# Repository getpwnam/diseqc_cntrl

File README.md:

# diseqc_cntrl

Ethernet-connected DiSEqC motor control interface for satellite LNB systems, built around an STM32F407 microcontroller.

## Disclaimer

This project is in active development and use is at your own risk. Core firmware,
managed deployment, X.509 provisioning, TLS 1.3, and read-only REST API flows
have been exercised on Cubley v0.5 hardware; this is not a production safety
certification.

## Quick Start

For the tested firmware-to-HTTPS path:

1. Build and flash the firmware.
2. Build and deploy `CubleyControl` over the nanoFramework wire protocol.
3. Provision a unique X.509 device credential.
4. Trust the public certificate and verify `/api/v2/health`.
5. Optionally configure an API token over the USB CDC console.

Follow [HTTPS Transport](docs/software/HTTPS_TRANSPORT.md) for the complete
copy-and-paste sequence. The API client is [tools/cubleyctl.py](tools/cubleyctl.py);
the API guide is
[DEVICE_API_V2_DEVELOPER_GUIDE.md](docs/software/DEVICE_API_V2_DEVELOPER_GUIDE.md).

## Introduction

Enables remote control of LNB power supply voltage (13 V / 18 V polarization selection), DiSEqC 1.x command generation, and IF signal routing — all manageable over a 10/100 Mbps Ethernet link or USB.

## Repository Structure

The project is intentionally split into separate domains:

1. `hardware/`  
	KiCad schematics, PCB layout, fabrication outputs, and hardware-specific assets.
2. `software/nanoFramework/`  
	Managed application + native integration layer used by this project.
3. `nf-interpreter` (external dependency at build time)  
	The nanoFramework/ChibiOS firmware base is cloned during build and patched with this repository's target files.

See:
- `hardware/README.md`
- `software/README.md`
- `software/nanoFramework/README.md`

## PCB

4-layer board (F.Cu / In1.Cu / In2.Cu / B.Cu) with split ground planes — digital GND, analog GNDA, and power PGND domains are connected via net ties at controlled star-ground points to minimise noise coupling into the LNB signal path.

## Hardware Overview

### Microcontroller

- **STM32F407VGT6** (ARM Cortex-M4, 168 MHz, 1 MB Flash, 192 KB RAM, LQFP-100)
- 8 MHz HSE crystal (ABLS-8.000MHZ-20-B-3-H-T) on PH0/PH1 with C15/C18 load capacitors
- Separate filtered +3V3_ANA rail for the on-chip ADC reference
- Status LED (green, 0603)

### Key peripherals used

| Peripheral | Function |
| --- | --- |
| I2C1 | LNBH26PQR LNB supply controller |
| I2C3 | FM24CL16B 16 Kb F-RAM and expansion header |
| Ethernet MAC (RMII) | LAN8742A 10/100 Ethernet PHY |
| TIM4 CH1 | DiSEqC 22 kHz tone generation |
| USART3 | Serial debug / expansion (pin header J2) |
| USB OTG FS | USB 2.0 device (USB-C) |
| SWD | Debug port (2×5 pin header J5) |

### Power Supply

**Input:** Barrel jack (RASM742TRX, 2.1 mm centre-positive)

Protection chain (in order):

1. **F1** — PTC resettable fuse (1812L075/33DR, 0.75 A hold / 33 V)
2. **D2** — SMBJ24D bidirectional TVS (24 V clamp)
3. **D1** — SS14F-HF Schottky diode (reverse polarity protection)

Regulation:

| Stage | Device | Topology | Output |
| --- | --- | --- | --- |
| 1 | PS1 (TPS560430XDBVR) | Synchronous buck (4.3–36 V in) | +12 V (feeds LNBH26PQR) |
| 2 | TPS560200DBVR | Buck (4.5–17 V in) | +3.3 V (digital logic) |

A filtered +3V3_ANA rail is derived from +3.3 V via a ferrite bead for the MCU analog supply.

### LNB Control — LNBH26PQR

- Dual LNB supply regulator with integrated step-up converter (ST LNBH26PQR, QFN-24)
- Powered from the +12 V rail
- Generates switchable 13 V / 18 V output for LNB polarization selection
- Built-in DiSEqC 1.x/2.x 22 kHz tone modulation, driven from TIM4 CH1
- Fault output routed to MCU GPIO
- External boost components: STPS130A Schottky, US1A rectifier, 33 µH inductor, 100 µF bulk caps
- DiSEqC envelope detection via BAT43XV2 small-signal Schottky
- ESD protection on coaxial outputs (RCLAMP0502BATCT)

### Ethernet

- STM32F407 integrated 10/100 Ethernet MAC connected over RMII
- **LAN8742A-CZ-TR** 10/100 Ethernet PHY (Microchip, SQFN-24)
- 25 MHz PHY crystal (ABLS-25.000MHZ-D-FT)
- **J0011D21BNL** RJ45 connector with integrated magnetics and link/activity LEDs

### USB

- **USB4110-GF-A** USB Type-C receptacle (USB 2.0)
- **USBLC6-2P6** ESD protection on D+/D−
- Connected to STM32 USB OTG FS peripheral

### Non-Volatile Storage

- **FM24CL16B-GTR** 16 Kb F-RAM (Infineon, I2C, SOIC-8)
- Unlimited write endurance — stores network configuration, LNB settings, and DiSEqC sequence parameters

### Connectors

| Ref | Type | Purpose |
| --- | --- | --- |
| J1 | Barrel jack (RASM742TRX) | DC power input |
| J2 | 1×4 pin header (2.00 mm) | USART3 serial header (+3V3, TX, RX, GND) |
| J3 | 1×4 pin header (2.00 mm) | I2C3 expansion header (+3V3, SCL, SDA, GND) |
| J4 | USB-C (USB4110-GF-A) | USB 2.0 device |
| J5 | 2×5 pin header (2.54 mm) | SWD debug |
| J6 | SMA edge-mount | IF input from LNB |
| J7 | SMA edge-mount | LNB output (power + DiSEqC + IF) |
| J9 | RJ45 (J0011D21BNL) | 10/100 Ethernet with integrated magnetics and LEDs |
| S1 | SPDT slide switch (PCM12SMTBR) | Mode / power select |

### Test Points

| Ref | Net | Purpose |
| --- | --- | --- |
| TP1 | VIN_FUSED | Input rail after PTC fuse |
| TP2 | +12V | Main regulated 12 V rail |
| TP3 | +3V3 | Main digital logic rail |
| TP4 | VIN_RAW | Input rail before fuse/protection chain |
| TP5 | VIN_PROTECTED | Input rail after TVS and reverse-polarity diode |
| TP6 | +3V3_ANA | Filtered analog 3.3 V rail |
| TP7 | VSSA | Analog ground reference |
| TP8 | /MCU/BOOT0 | MCU BOOT0 strap node |
| TP9 | VBUS | USB VBUS (5 V) |
| TP10 | /MCU/CC1 | USB-C CC1 configuration channel |
| TP11 | /MCU/CC2 | USB-C CC2 configuration channel |
| TP12 | IF_OUT | IF signal path node |
| TP13 | LNB_OUT | LNB output node |
| TP14 | /MCU/LNBH26PQR/LNB_FLT | LNB controller fault signal |

### Protection

| Component | Type | Location |
| --- | --- | --- |
| F1 (1812L075/33DR) | PTC fuse, 0.75 A / 33 V | Power input |
| D2 (SMBJ24D) | 24 V bidirectional TVS | After fuse |
| D1 (SS14F-HF) | Schottky reverse polarity | After TVS |
| IC3 (USBLC6-2P6) | USB ESD clamp | USB D+/D− |
| D7 (RCLAMP0502BATCT) | ESD / CDE clamp | LNB coaxial I/O |

## Design Notes

- 4-layer PCB with split ground planes joined at star-ground net ties
- Predominantly 0603 passives throughout
- 3D models (STEP) provided for all major components
- Gerbers exported to `fab/gerber/`
- All Mouser part numbers embedded in schematic symbols for direct BOM procurement
- Crystal load-capacitor values are documented on schematic and periodically re-validated against crystal load specs and board parasitics

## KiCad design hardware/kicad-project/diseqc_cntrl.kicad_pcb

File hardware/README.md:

# Hardware Domain

This directory contains the board design and fabrication assets for the DiSEqC controller.

## Contents

- `kicad-project/`
  - Source-of-truth schematics and PCB layout.
- `gerber/`
  - Fabrication outputs for PCB manufacturing.
- `nonfree/`
  - Third-party footprints/models/symbols and their licenses.
- `LICENSE.txt`
  - Hardware licensing information.

## Working Rules

- Treat KiCad files in `kicad-project/` as canonical.
- Regenerate Gerbers from the matching KiCad revision before manufacturing.
- Keep hardware-specific docs/assets in `hardware/` to avoid cross-domain drift.

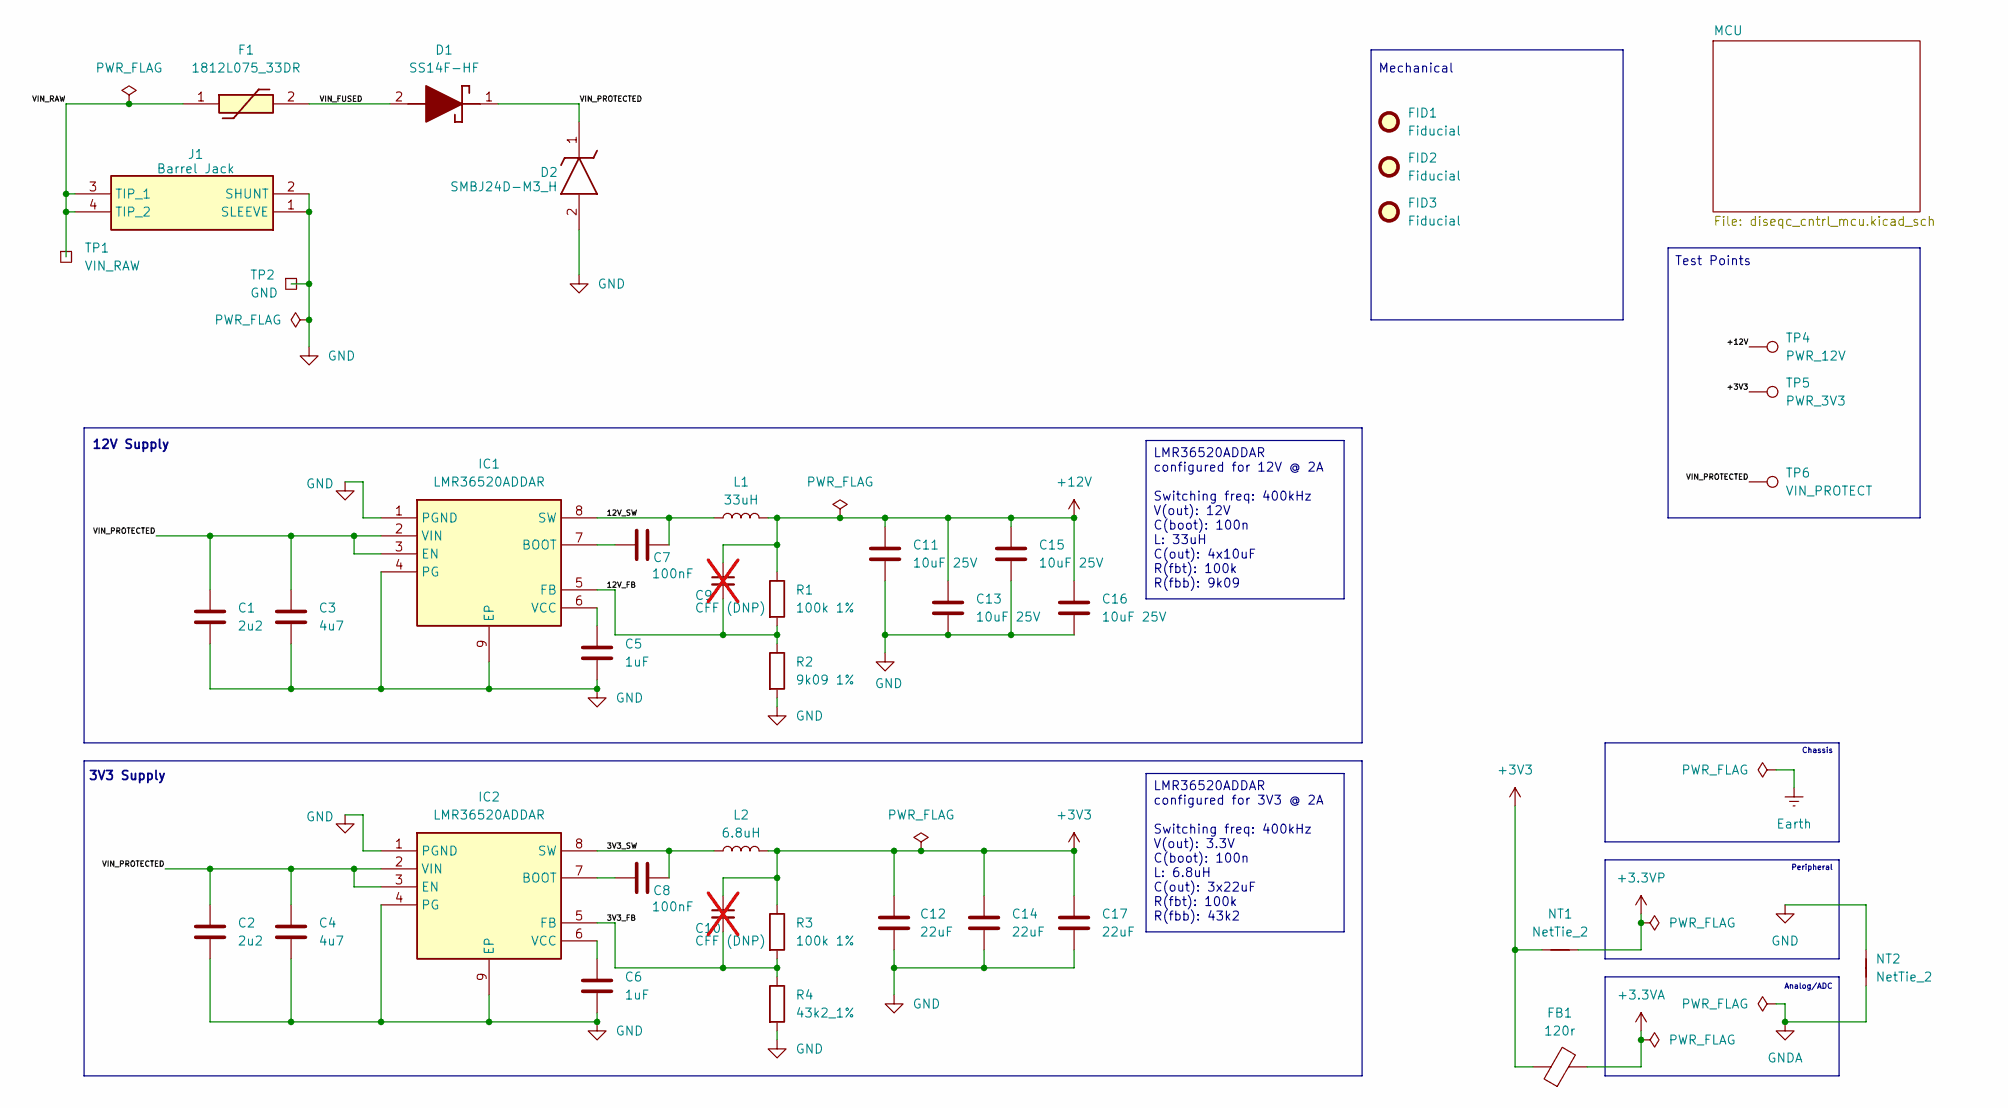
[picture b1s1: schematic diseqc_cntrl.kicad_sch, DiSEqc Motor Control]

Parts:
C1, C2: 2u2; C_0603_1608Metric; Part EMK063B7103KP-F; Mouser Part Number 81-GRM188R6YA225MA2D
C3, C4: 4u7; C_0603_1608Metric
C5, C6: 1uF; C_0603_1608Metric
C7, C8: 100nF; C_0603_1608Metric; Part EMK063B7103KP-F
C9, C10: CFF (DNP); not fitted
C11, C13, C15, C16: 10uF 25V; C_1206_3216Metric
C12, C14, C17: 22uF; C_0603_1608Metric; Tolerance 20%
D1: SS14F-HF; SODFL4626X120N; Mouser Part Number 750-SS14F-HF
D2: SMBJ24D-M3_H; DIOM5436X244N; Mouser Part Number 78-SMBJ24D-M3H
F1: 1812L075_33DR; 1812L010DR; Mouser Part Number 576-1812L075/33DR
FB1: 120r; L_0603_1608Metric
FID1, FID2, FID3: Fiducial; Fiducial_1mm_Mask2mm
IC1, IC2: LMR36520ADDAR; SOIC127P600X170-9N; Mouser Part Number 595-LMR36520ADDAR
J1: Barrel Jack; RASM742TRX; Mouser Part Number 502-RASM742TRX
L1: 33uH; WE-PD_1260_1245_1280_121054
L2: 6.8uH; INDPM5752X300N; Tolerance 20%
NT1, NT2: NetTie_2; NetTie-2_SMD_Pad2.0mm
R1, R3: 100k 1%; R_0603_1608Metric; Tolerance 1%; ToleranceRequirement <=1%
R2: 9k09 1%; R_0603_1608Metric
R4: 43k2_1%; R_0603_1608Metric; ToleranceRequirement <=1%
TP1: VIN_RAW; TestPoint_Pad_4.0x4.0mm
TP2: GND; TestPoint_Pad_4.0x4.0mm
TP4: PWR_12V; TestPoint_THTPad_D1.0mm_Drill0.5mm_annotated
TP5: PWR_3V3; TestPoint_THTPad_D1.0mm_Drill0.5mm_annotated
TP6: VIN_PROTECT; TestPoint_THTPad_D1.0mm_Drill0.5mm_annotated

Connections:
+3.3VA: FB1.2; also elsewhere on the board
+3.3VP: NT1.2; also elsewhere on the board
+3V3: C10.1, C12.1, C14.1, C17.1, FB1.1, L2.2, NT1.1, R3.1, TP5.1 (1_1); also elsewhere on the board
+12V: C9.1, C11.1, C13.1, C15.1, C16.1, L1.2, R1.1, TP4.1 (1_1); also elsewhere on the board
/3V3_FB: C10.2, IC2.5 (FB), R3.2, R4.1
/3V3_SW: C8.2, IC2.8 (SW), L2.1
/12V_FB: C9.2, IC1.5 (FB), R1.2, R2.1
/12V_SW: C7.2, IC1.8 (SW), L1.1
/VIN_FUSED: D1.2 (A), F1.2
/VIN_PROTECTED: C1.1, C2.1, C3.1, C4.1, D1.1 (K), D2.1 (K), IC1.2 (VIN), IC1.3 (EN), IC2.2 (VIN), IC2.3 (EN), TP6.1 (1_1)
/VIN_RAW: F1.1, J1.3 (TIP_1), J1.4 (TIP_2), TP1.1 (1_1)
GND: C1.2, C2.2, C3.2, C4.2, C5.2, C6.2, C11.2, C12.2, C13.2, C14.2, C15.2, C16.2, C17.2, D2.2 (A), IC1.1 (PGND), IC1.4 (PG), IC1.9 (EP), IC2.1 (PGND), IC2.4 (PG), IC2.9 (EP), J1.1 (SLEEVE), J1.2 (SHUNT), NT2.2, R2.2, R4.2, TP2.1 (1_1); also elsewhere on the board
GNDA: NT2.1; also elsewhere on the board
unnamed: C7.1, IC1.7 (BOOT)
unnamed: C5.1, IC1.6 (VCC)
unnamed: C8.1, IC2.7 (BOOT)
unnamed: C6.1, IC2.6 (VCC)

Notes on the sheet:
3V3 Supply
Test Points
12V Supply
Analog/ADC
Peripheral
Mechanical
Chassis
LMR36520ADDAR configured for 3V3 @ 2A Switching freq: 400kHz V(out): 3.3V C(boot): 100n L: 6.8uH C(out): 3x22uF R(fbt): 100k R(fbb): 43k2
LMR36520ADDAR configured for 12V @ 2A Switching freq: 400kHz V(out): 12V C(boot): 100n L: 33uH C(out): 4x10uF R(fbt): 100k R(fbb): 9k09

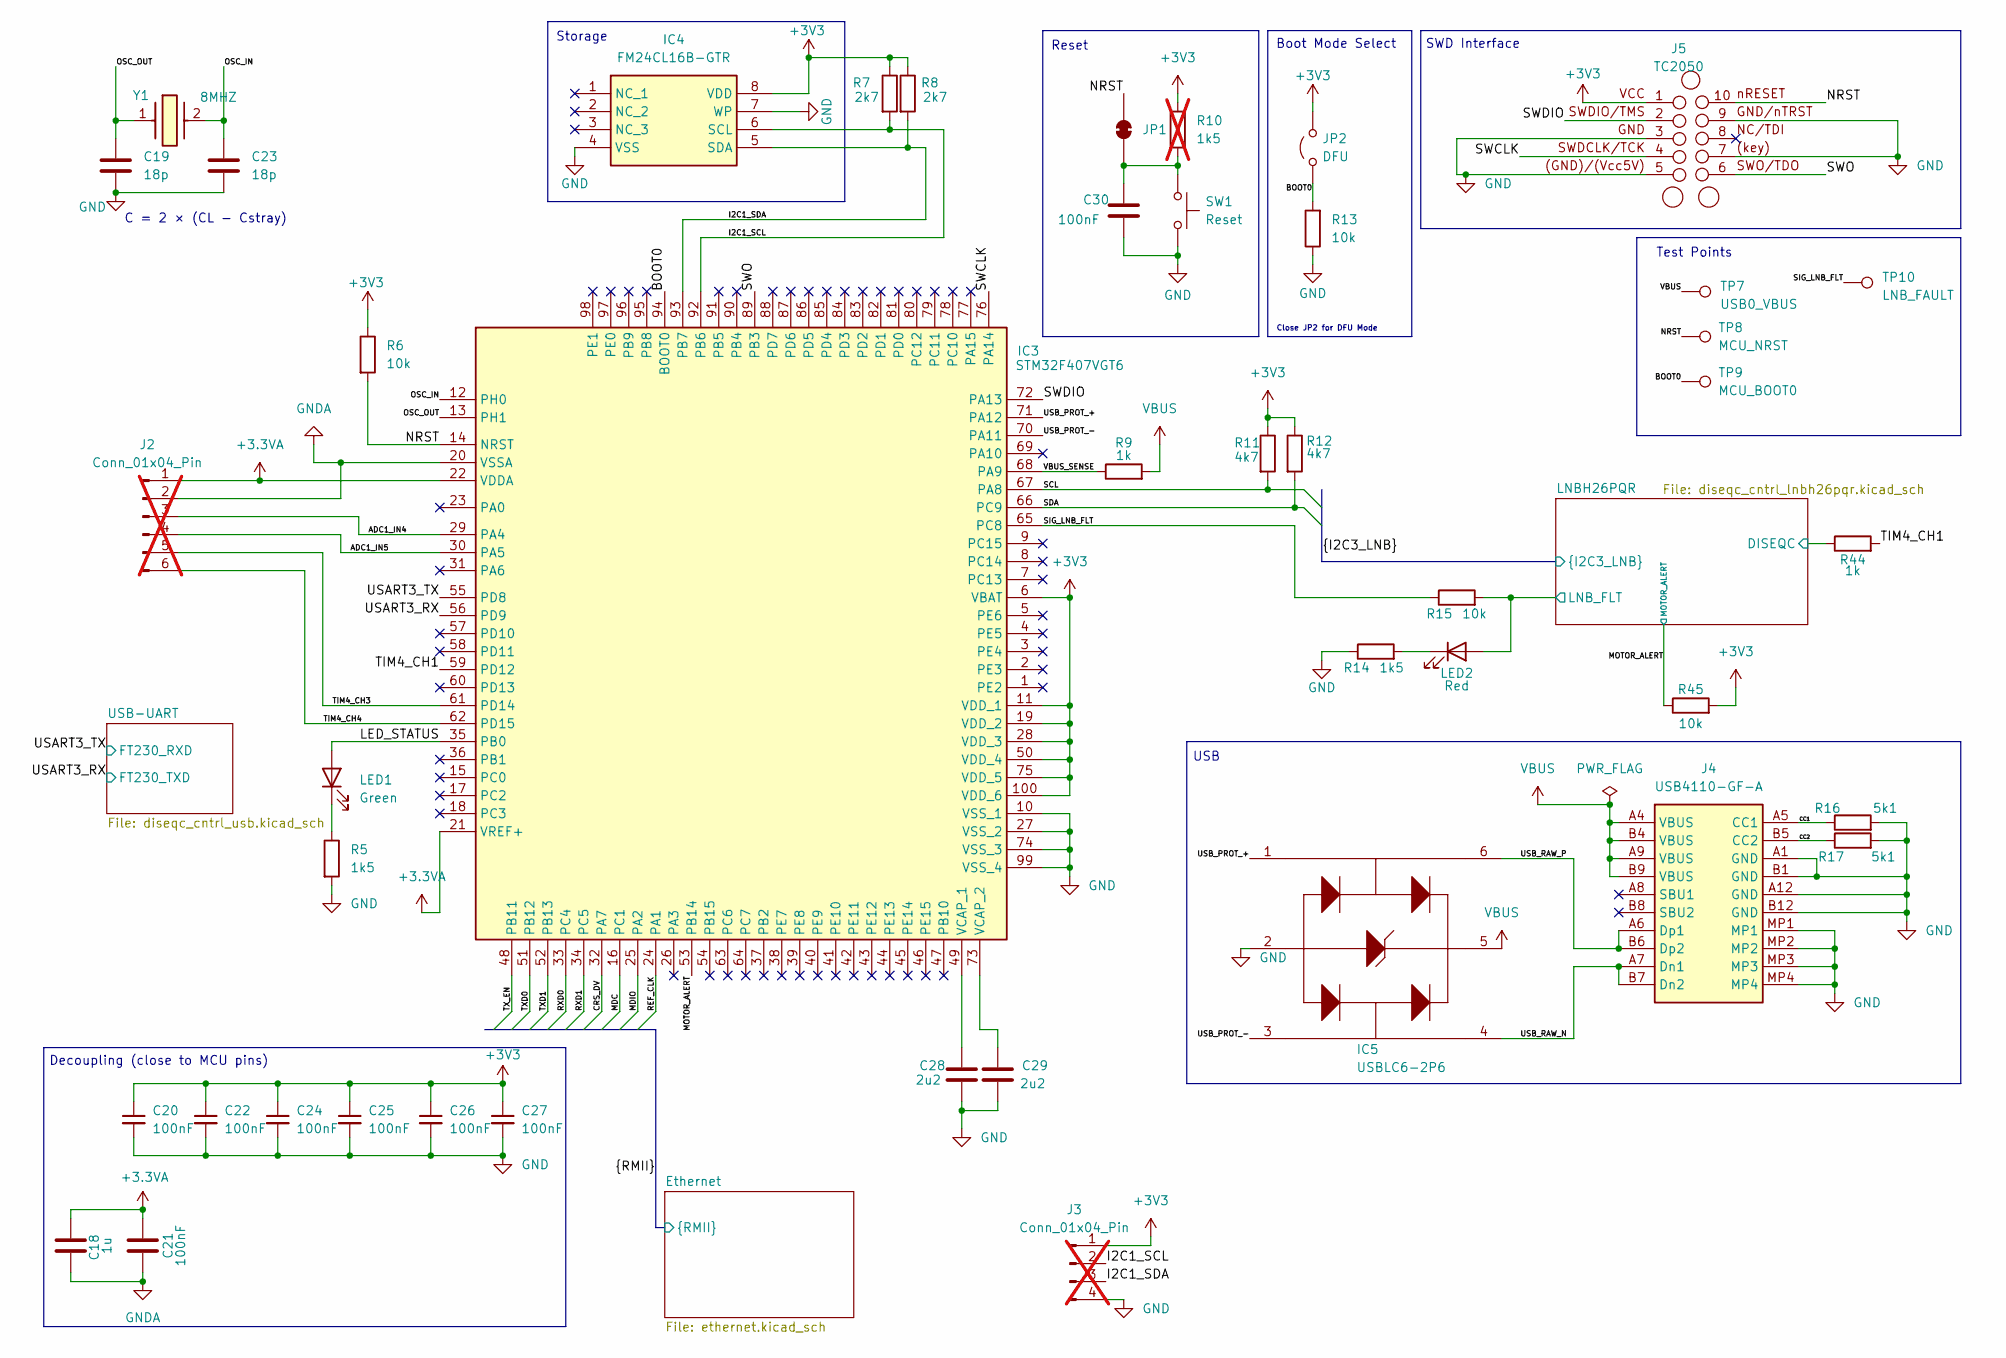
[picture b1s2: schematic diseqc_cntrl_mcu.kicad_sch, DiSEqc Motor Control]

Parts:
C18: 1u; C_0603_1608Metric; Mouser Part Number 81-GRM39R105K10
C19, C23: 18p; C_0603_1608Metric; Manufacturer_Part_Number 600S180JT250XT; Mouser Part Number 581-06031A180CAT2A
C20, C21, C22, C24, C25, C26, C27, C30: 100nF; C_0603_1608Metric
C28, C29: 2u2; C_0603_1608Metric; Mouser Part Number 81-GRM188R6YA225MA2D
IC3: STM32F407VGT6; QFP50P1600X1600X160-100N; Mouser Part Number 511-STM32F407VGT6
IC4: FM24CL16B-GTR; SOIC127P602X173-8N; Mouser Part Number 877-FM24CL16B-GTR
IC5: USBLC6-2P6; USBLC62P6; Mouser Part Number 511-USBLC6-2P6
J2: Conn_01x04_Pin; PinHeader_2x03_P2.54mm_Vertical_SMD; Mouser Part Number 200-TMM10501TSSM; not fitted
J3: Conn_01x04_Pin; PinHeader_1x04_P2.00mm_Vertical_SMD_Pin1Left; Mouser Part Number 200-TMM10501TSSM; not fitted
J4: USB4110-GF-A; USB4110GFA; Mouser Part Number 640-USB4110-GF-A
J5: TC2050; Tag-Connect_TC2050-IDC-FP_2x05_P1.27mm_Vertical
JP1: SolderJumper_2_Bridged; SolderJumper-2_P1.3mm_Bridged_Pad1.0x1.5mm
JP2: DFU; PinHeader_1x02_P2.54mm_Vertical
LED1: Green; LED_0603_1608Metric; Mouser Part Number 604-APG1608ZGC
LED2: Red; LED_0603_1608Metric
R5: 1k5; R_0603_1608Metric; Mouser Part Number 603-AC0603JR-071K5L
R6, R15, R45: 10k; R_0603_1608Metric
R7, R8: 2k7; R_0603_1608Metric; Mouser Part Number 603-AR0603JR-072K7L
R9, R44: 1k; R_0603_1608Metric; Tolerance 5%
R10: 1k5; R_0603_1608Metric; not fitted
R11, R12: 4k7; R_0603_1608Metric; Mouser Part Number 603-AC0603FR-074K7L
R13: 10k; R_0603_1608Metric; Mouser Part Number 603-RC0603DR-0710KL
R14: 1k5; R_0603_1608Metric
R16, R17: 5k1; R_0603_1608Metric; Mouser Part Number 603-RC0603FR-075K1P
SW1: Reset; 95C04B3GWRT
TP7: USB0_VBUS; TestPoint_THTPad_D1.0mm_Drill0.5mm_annotated
TP8: MCU_NRST; TestPoint_THTPad_D1.0mm_Drill0.5mm_annotated
TP9: MCU_BOOT0; TestPoint_THTPad_D1.0mm_Drill0.5mm_annotated
TP10: LNB_FAULT; TestPoint_THTPad_D1.0mm_Drill0.5mm_annotated
Y1: 8MHZ; ABLS8000MHz20B3HT; Mouser Part Number 815-LS8000MHZ20B3HT

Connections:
+3.3VA: C18.1, C21.2, IC3.21 (VREF+), IC3.22 (VDDA), J2.1; also elsewhere on the board
+3V3: C20.1, C22.1, C24.1, C25.1, C26.1, C27.1, IC3.6 (VBAT), IC3.11 (VDD_1), IC3.19 (VDD_2), IC3.28 (VDD_3), IC3.50 (VDD_4), IC3.75 (VDD_5), IC3.100 (VDD_6), IC4.8 (VDD), J3.1, J5.1 (VCC), JP2.2 (B), R6.1, R7.1, R8.1, R10.1, R11.1, R12.1, R45.2; also elsewhere on the board
/MCU/ADC1_IN4: IC3.29 (PA4), J2.3
/MCU/ADC1_IN5: IC3.30 (PA5), J2.4
/MCU/BOOT0: IC3.94 (BOOT0), JP2.1 (A), R13.2, TP9.1 (1_1)
/MCU/CC1: J4.A5 (CC1), R16.1
/MCU/CC2: J4.B5 (CC2), R17.1
/MCU/CRS_DV: IC3.32 (PA7); also elsewhere on the board
/MCU/I2C1_SCL: IC3.92 (PB6), IC4.6 (SCL), J3.2, R7.2
/MCU/I2C1_SDA: IC3.93 (PB7), IC4.5 (SDA), J3.3, R8.2
/MCU/LED_STATUS: IC3.35 (PB0), LED1.2 (A)
/MCU/LNBH26PQR/DISEQC: R44.1; also elsewhere on the board
/MCU/LNBH26PQR/LNB_FLT: LED2.2 (A), R15.2; also elsewhere on the board
/MCU/MDC: IC3.16 (PC1); also elsewhere on the board
/MCU/MDIO: IC3.25 (PA2); also elsewhere on the board
/MCU/MOTOR_ALERT: IC3.53 (PB14), R45.1; also elsewhere on the board
/MCU/NRST: IC3.14 (NRST), J5.10 (nRESET), JP1.2 (B), R6.2, TP8.1 (1_1); also elsewhere on the board
/MCU/OSC_IN: C23.1, IC3.12 (PH0), Y1.2
/MCU/OSC_OUT: C19.1, IC3.13 (PH1), Y1.1
/MCU/REF_CLK: IC3.24 (PA1); also elsewhere on the board
/MCU/RXD0: IC3.33 (PC4); also elsewhere on the board
/MCU/RXD1: IC3.34 (PC5); also elsewhere on the board
/MCU/SCL: IC3.67 (PA8), R11.2; also elsewhere on the board
/MCU/SDA: IC3.66 (PC9), R12.2; also elsewhere on the board
/MCU/SIG_LNB_FLT: IC3.65 (PC8), R15.1, TP10.1 (1_1)
/MCU/SWCLK: IC3.76 (PA14), J5.4 (SWDCLK/TCK)
/MCU/SWDIO: IC3.72 (PA13), J5.2 (SWDIO/TMS)
/MCU/SWO: IC3.89 (PB3), J5.6 (SWO/TDO)
/MCU/TIM4_CH1: IC3.59 (PD12), R44.2
/MCU/TIM4_CH3: IC3.61 (PD14), J2.5
/MCU/TIM4_CH4: IC3.62 (PD15), J2.6
/MCU/TXD0: IC3.51 (PB12); also elsewhere on the board
/MCU/TXD1: IC3.52 (PB13); also elsewhere on the board
/MCU/TX_EN: IC3.48 (PB11); also elsewhere on the board
/MCU/USART3_RX: IC3.56 (PD9); also elsewhere on the board
/MCU/USART3_TX: IC3.55 (PD8); also elsewhere on the board
/MCU/USB_PROT_+: IC3.71 (PA12), IC5.1 (I/O1_1)
/MCU/USB_PROT_-: IC3.70 (PA11), IC5.3 (I/O2_1)
/MCU/USB_RAW_N: IC5.4 (I/O2_2), J4.A7 (Dn1), J4.B7 (Dn2)
/MCU/USB_RAW_P: IC5.6 (I/O1_2), J4.A6 (Dp1), J4.B6 (Dp2)
/MCU/VBUS_SENSE: IC3.68 (PA9), R9.1
GND: C19.2, C20.2, C22.2, C23.2, C24.2, C25.2, C26.2, C27.2, C28.2, C29.1, C30.2, IC3.10 (VSS_1), IC3.27 (VSS_2), IC3.74 (VSS_3), IC3.99 (VSS_4), IC4.4 (VSS), IC4.7 (WP), IC5.2 (GND), J3.4, J4.A1 (GND), J4.A12 (GND), J4.B1 (GND), J4.B12 (GND), J4.MP1, J4.MP2, J4.MP3, J4.MP4, J5.3 (GND), J5.5 ((GND)/(Vcc5V)), J5.7 ((key)), J5.9 (GND/nTRST), R5.2, R13.1, R14.1, R16.2, R17.2, SW1.T2; also elsewhere on the board
GNDA: C18.2, C21.1, IC3.20 (VSSA), J2.2; also elsewhere on the board
unnamed: C28.1, IC3.49 (VCAP_1)
unnamed: C29.2, IC3.73 (VCAP_2)
unnamed: C30.1, JP1.1 (A), R10.2, SW1.T1
unnamed: LED1.1 (K), R5.1
unnamed: LED2.1 (K), R14.2
VBUS: IC5.5 (VBUS), J4.A4 (VBUS), J4.A9 (VBUS), J4.B4 (VBUS), J4.B9 (VBUS), R9.2, TP7.1 (1_1)

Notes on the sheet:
C = 2 × (CL - Cstray)
Reset
Close JP2 for DFU Mode
Storage
SWD Interface
USB
Boot Mode Select
Decoupling (close to MCU pins)
Test Points

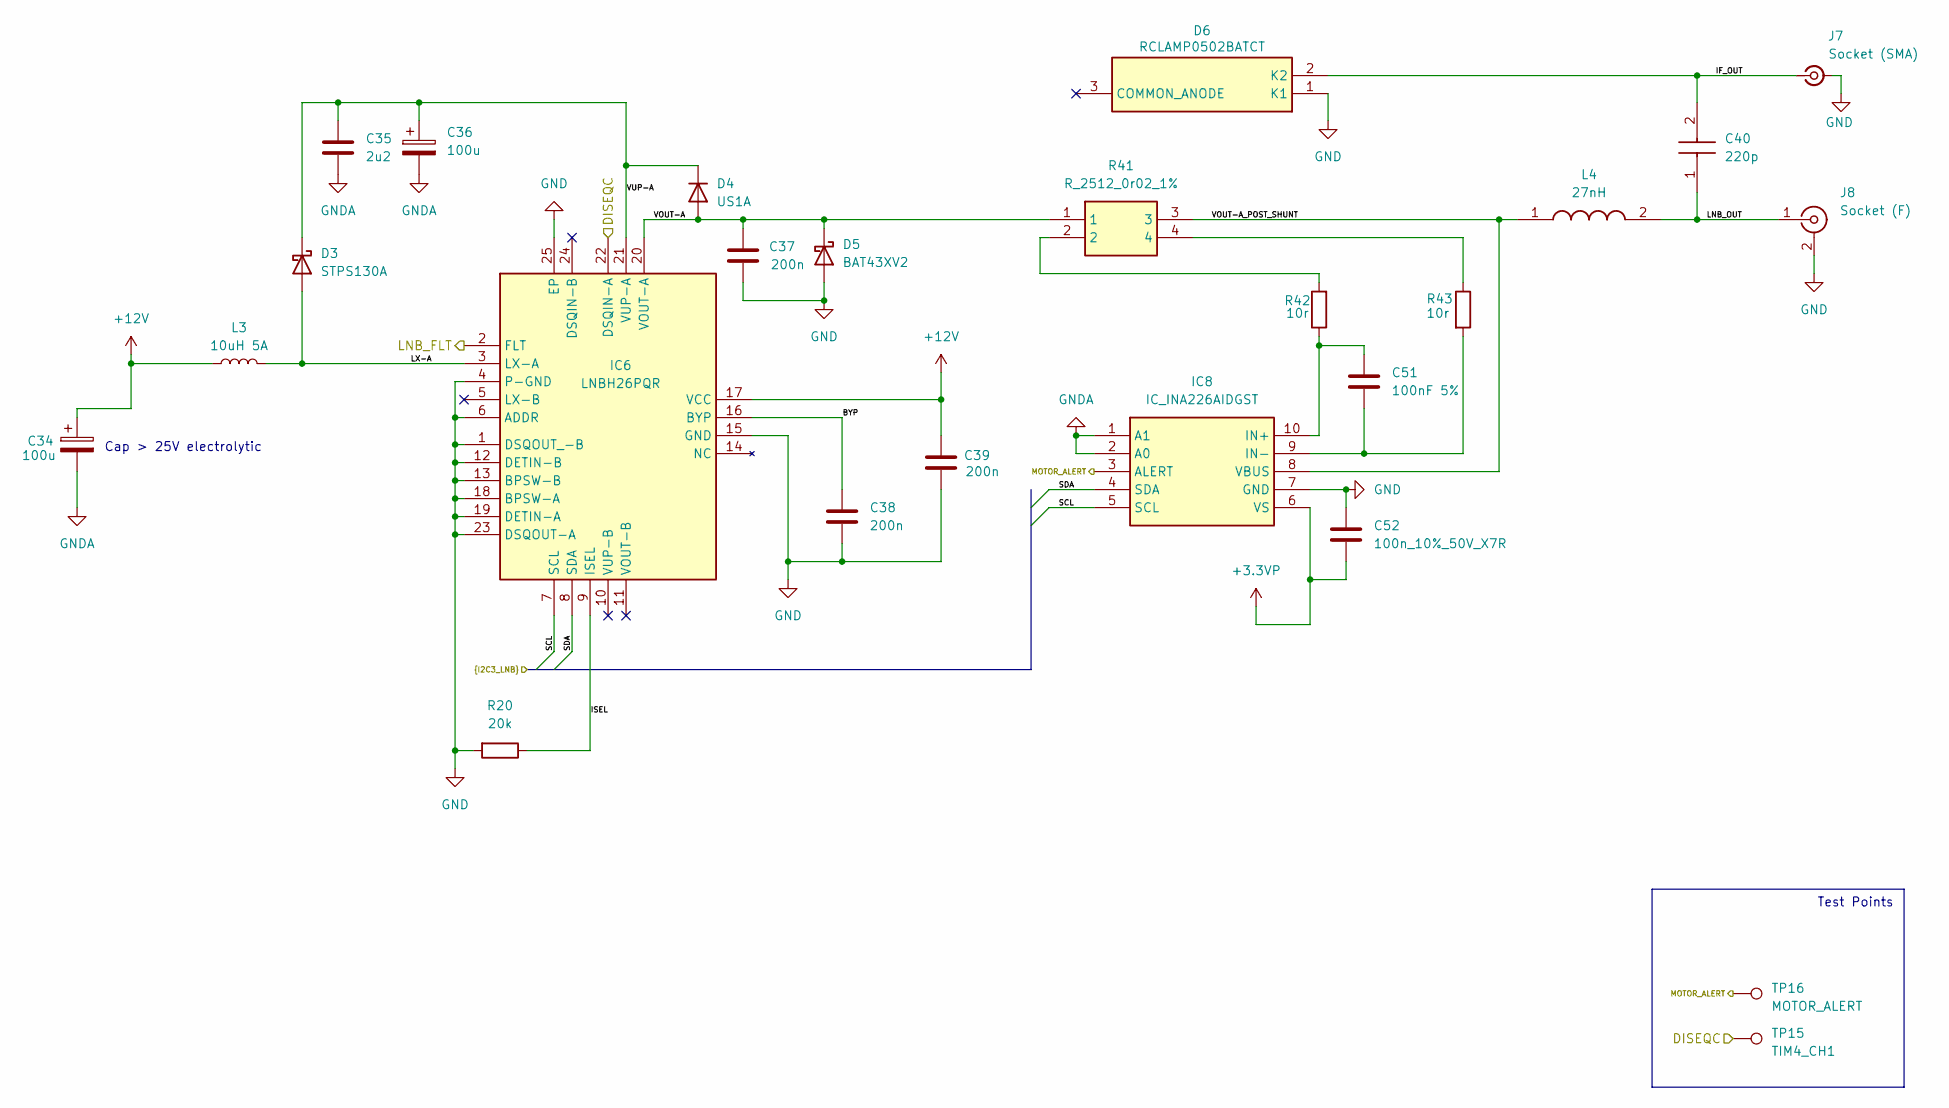
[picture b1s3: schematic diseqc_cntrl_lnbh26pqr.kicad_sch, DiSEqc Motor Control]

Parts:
C34, C36: 100u; CAPAE660X770N; Mouser Part Number 710-865080445010
C35: 2u2; C_0603_1608Metric; Mouser Part Number 81-GRM188R6YA225MA2D
C37, C38, C39: 200n; C_0603_1608Metric; Mouser Part Number 791-0603B204K160CT
C40: 220p; C_0603_1608Metric; Mouser Part Number 81-GRM185C2A221JA01D
C51: 100nF 5%; C_0603_1608Metric; Tolerance 10%
C52: 100n_10%_50V_X7R; C_0603_1608Metric
D3: STPS130A; STTH2R02AY; Mouser Part Number 511-STPS130A
D4: US1A; D_SMA; Mouser Part Number 637-US1A
D5: BAT43XV2; SODFL1608X70N; Mouser Part Number 512-BAT43XV2
D6: RCLAMP0502BATCT; SOT50P160X90-3N; Mouser Part Number 947-RCLAMP0502BATCT
IC6: LNBH26PQR; QFN50P400X400X100-25N-D; Manufacturer_Part_Number LNBH26PQR; Mouser Part Number 511-LNBH26PQR
IC8: IC_INA226AIDGST; TSSOP-10_3x3mm_P0.5mm; Mouser Part Number 595-INA226AIDGST
J7: Socket (SMA); SMA_Molex_73251-1153_EdgeMount_Horizontal; Mouser Part Number 538-73251-1153
J8: Socket (F); AMPHENOL_531-40156; Maufacturer_Part_Number 531-40156; Mouser Part Number 523-531-40156
L3: 10uH 5A; SRP6060FA4R7M
L4: 27nH; 0603DC27NXJRW; Mouser Part Number 994-0603DC-27NXJRW
R20: 20k; R_0603_1608Metric; Tolerance 1%; Mouser Part Number 603-RC0603JR-07100KL
R41: R_2512_0r02_1%; WSK2512R0100FEA; Mouser Part Number 71-WSK2512R0200FEA
R42, R43: 10r; R_0603_1608Metric; Tolerance 5%
TP15: TIM4_CH1; TestPoint_THTPad_D1.0mm_Drill0.5mm_annotated
TP16: MOTOR_ALERT; TestPoint_THTPad_D1.0mm_Drill0.5mm_annotated

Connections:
+3.3VP: C52.1, IC8.6 (VS); also elsewhere on the board
+12V: C34.1, C39.2, IC6.17 (VCC), L3.1; also elsewhere on the board
/MCU/LNBH26PQR/BYP: C38.2, IC6.16 (BYP)
/MCU/LNBH26PQR/DISEQC: IC6.22 (DSQIN-A), TP15.1 (1_1); also elsewhere on the board
/MCU/LNBH26PQR/IF_OUT: C40.2, D6.2 (K2), J7.1 (In)
/MCU/LNBH26PQR/ISEL: IC6.9 (ISEL), R20.1
/MCU/LNBH26PQR/LNB_FLT: IC6.2 (FLT); also elsewhere on the board
/MCU/LNBH26PQR/LNB_OUT: C40.1, J8.1 (In), L4.2
/MCU/LNBH26PQR/LX-A: D3.2 (A), IC6.3 (LX-A), L3.2
/MCU/LNBH26PQR/VOUT-A: C37.1, D4.2 (A), D5.1 (K), IC6.20 (VOUT-A), R41.1
/MCU/LNBH26PQR/VOUT-A_POST_SHUNT: IC8.8 (VBUS), L4.1, R41.3
/MCU/LNBH26PQR/VUP-A: C35.1, C36.1, D3.1 (K), D4.1 (K), IC6.21 (VUP-A)
/MCU/MOTOR_ALERT: IC8.3 (ALERT), TP16.1 (1_1); also elsewhere on the board
/MCU/SCL: IC6.7 (SCL), IC8.5 (SCL); also elsewhere on the board
/MCU/SDA: IC6.8 (SDA), IC8.4 (SDA); also elsewhere on the board
GND: C37.2, C38.1, C39.1, C52.2, D5.2 (A), D6.1 (K1), IC6.1 (DSQOUT_-B), IC6.4 (P-GND), IC6.6 (ADDR), IC6.12 (DETIN-B), IC6.13 (BPSW-B), IC6.15 (GND), IC6.18 (BPSW-A), IC6.19 (DETIN-A), IC6.23 (DSQOUT-A), IC6.25 (EP), IC8.7 (GND), J7.2 (Ext), J8.2 (Ext), R20.2; also elsewhere on the board
GNDA: C34.2, C35.2, C36.2, IC8.1 (A1), IC8.2 (A0); also elsewhere on the board
unnamed: C51.1, IC8.10 (IN+), R42.1
unnamed: C51.2, IC8.9 (IN-), R43.2
unnamed: R41.2, R42.2
unnamed: R41.4, R43.1

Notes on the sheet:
Cap > 25V electrolytic
Test Points

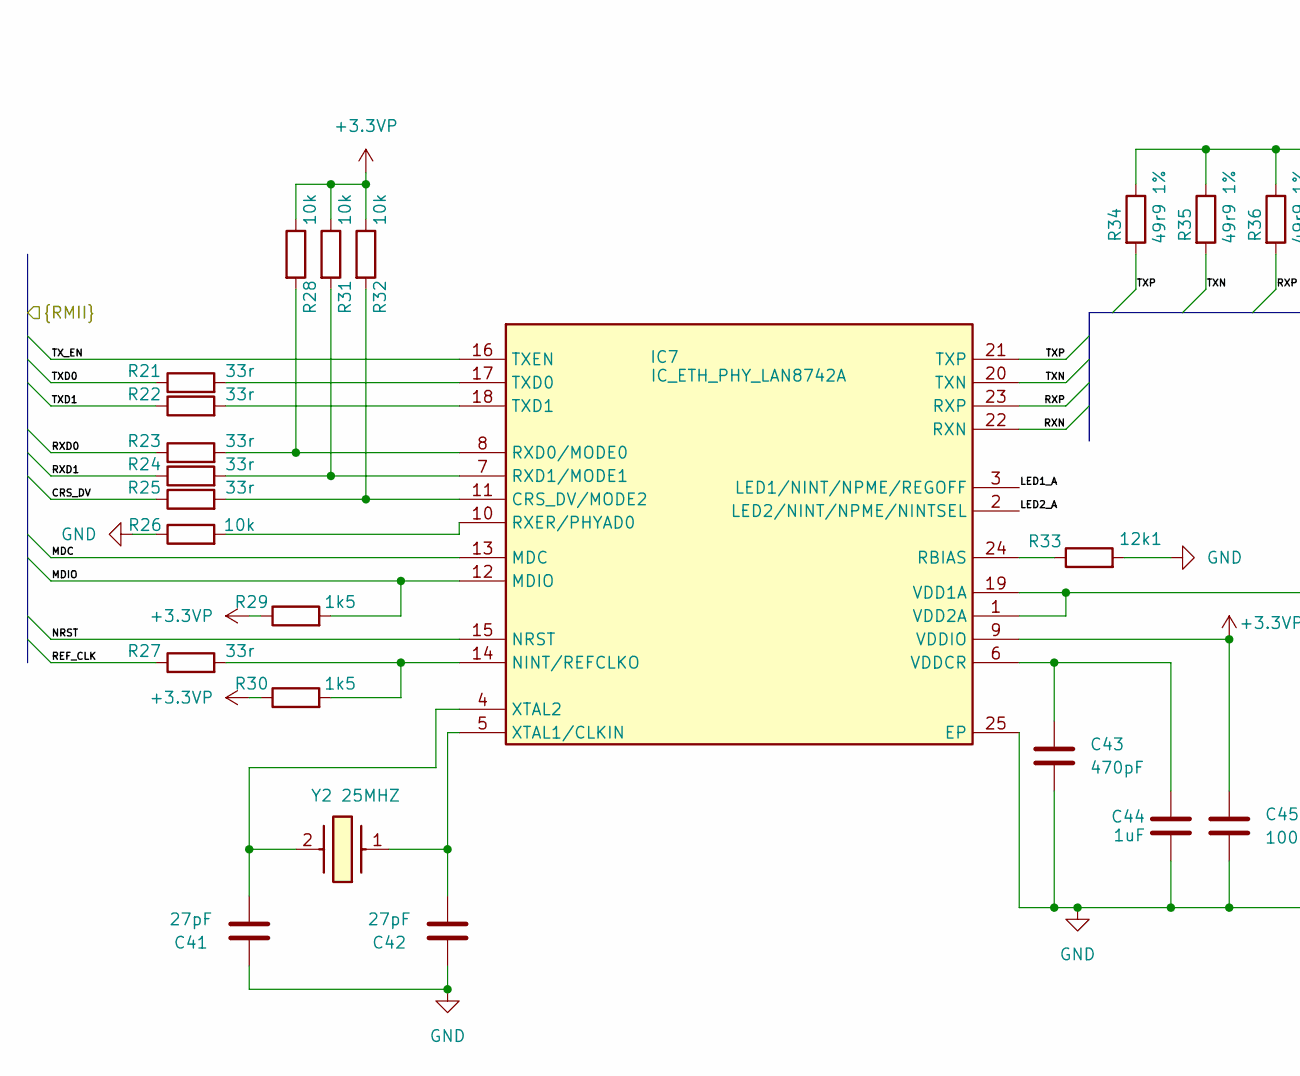
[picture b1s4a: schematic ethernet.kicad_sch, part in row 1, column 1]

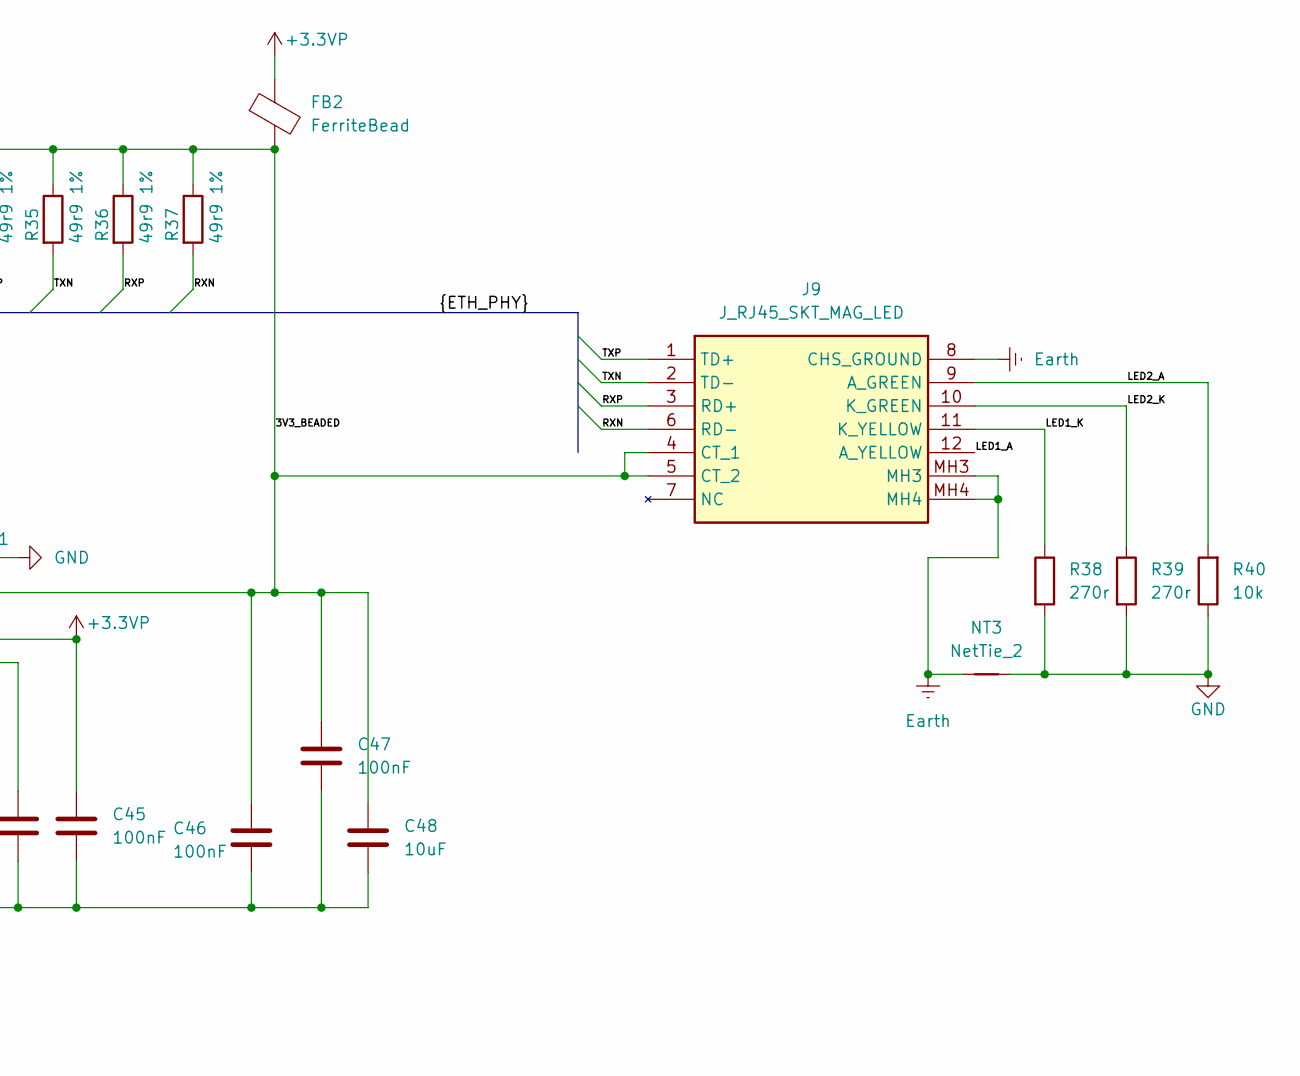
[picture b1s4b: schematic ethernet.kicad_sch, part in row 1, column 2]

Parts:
C41, C42: 27pF; C_0603_1608Metric; Tolerance 5%
C43: 470pF; C_0603_1608Metric
C44: 1uF; C_0603_1608Metric
C45, C46, C47: 100nF; C_0603_1608Metric
C48: 10uF; C_0603_1608Metric
FB2: FerriteBead; L_0603_1608Metric
IC7: IC_ETH_PHY_LAN8742A; VQFN-24-1EP_4x4mm_P0.5mm_EP2.5x2.5mm_ThermalVias; Mouser Part Number 579-LAN8742A-CZ-TR
J9: J_RJ45_SKT_MAG_LED; J0011D21BNL; Mouser Part Number 673-J0011D21BNL
NT3: NetTie_2; NetTie-2_SMD_Pad2.0mm
R21, R22, R23, R24, R25, R27: 33r; R_0603_1608Metric
R26, R28, R31, R32, R40: 10k; R_0603_1608Metric
R29, R30: 1k5; R_0603_1608Metric
R33: 12k1; R_0603_1608Metric
R34, R35, R36, R37: 49r9 1%; R_0603_1608Metric; Tolerance 1%
R38, R39: 270r; R_0603_1608Metric; Tolerance 5%
Y2: 25MHZ; ABLS25000MHZDFT; Mouser Part Number 815-ABLS25.MHZDFT

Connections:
+3.3VP: C45.1, FB2.1, IC7.9 (VDDIO), R28.1, R29.1, R30.1, R31.1, R32.1; also elsewhere on the board
/MCU/CRS_DV: R25.1; also elsewhere on the board
/MCU/Ethernet/3V3_BEADED: C46.1, C47.1, C48.1, FB2.2, IC7.1 (VDD2A), IC7.19 (VDD1A), J9.4 (CT_1), J9.5 (CT_2), R34.1, R35.1, R36.1, R37.1
/MCU/Ethernet/LED1_A: IC7.3 (LED1/NINT/NPME/REGOFF), J9.12 (A_YELLOW)
/MCU/Ethernet/LED1_K: J9.11 (K_YELLOW), R38.1
/MCU/Ethernet/LED2_A: IC7.2 (LED2/NINT/NPME/NINTSEL), J9.9 (A_GREEN), R40.2
/MCU/Ethernet/LED2_K: J9.10 (K_GREEN), R39.1
/MCU/Ethernet/RXN: IC7.22 (RXN), J9.6 (RD-), R37.2
/MCU/Ethernet/RXP: IC7.23 (RXP), J9.3 (RD+), R36.2
/MCU/Ethernet/TXN: IC7.20 (TXN), J9.2 (TD-), R35.2
/MCU/Ethernet/TXP: IC7.21 (TXP), J9.1 (TD+), R34.2
/MCU/MDC: IC7.13 (MDC); also elsewhere on the board
/MCU/MDIO: IC7.12 (MDIO), R29.2; also elsewhere on the board
/MCU/NRST: IC7.15 (NRST); also elsewhere on the board
/MCU/REF_CLK: R27.1; also elsewhere on the board
/MCU/RXD0: R23.1; also elsewhere on the board
/MCU/RXD1: R24.1; also elsewhere on the board
/MCU/TXD0: R21.1; also elsewhere on the board
/MCU/TXD1: R22.1; also elsewhere on the board
/MCU/TX_EN: IC7.16 (TXEN); also elsewhere on the board
Earth: J9.8 (CHS_GROUND), J9.MH3, J9.MH4, NT3.1
GND: C41.1, C42.1, C43.2, C44.2, C45.2, C46.2, C47.2, C48.2, IC7.25 (EP), NT3.2, R26.1, R33.2, R38.2, R39.2, R40.1; also elsewhere on the board
unnamed: IC7.11 (CRS_DV/MODE2), R25.2, R32.2
unnamed: IC7.14 (NINT/REFCLKO), R27.2, R30.2
unnamed: IC7.24 (RBIAS), R33.1
unnamed: IC7.8 (RXD0/MODE0), R23.2, R28.2
unnamed: IC7.7 (RXD1/MODE1), R24.2, R31.2
unnamed: IC7.10 (RXER/PHYAD0), R26.2
unnamed: IC7.17 (TXD0), R21.2
unnamed: IC7.18 (TXD1), R22.2
unnamed: C43.1, C44.1, IC7.6 (VDDCR)
unnamed: C42.2, IC7.5 (XTAL1/CLKIN), Y2.1
unnamed: C41.2, IC7.4 (XTAL2), Y2.2

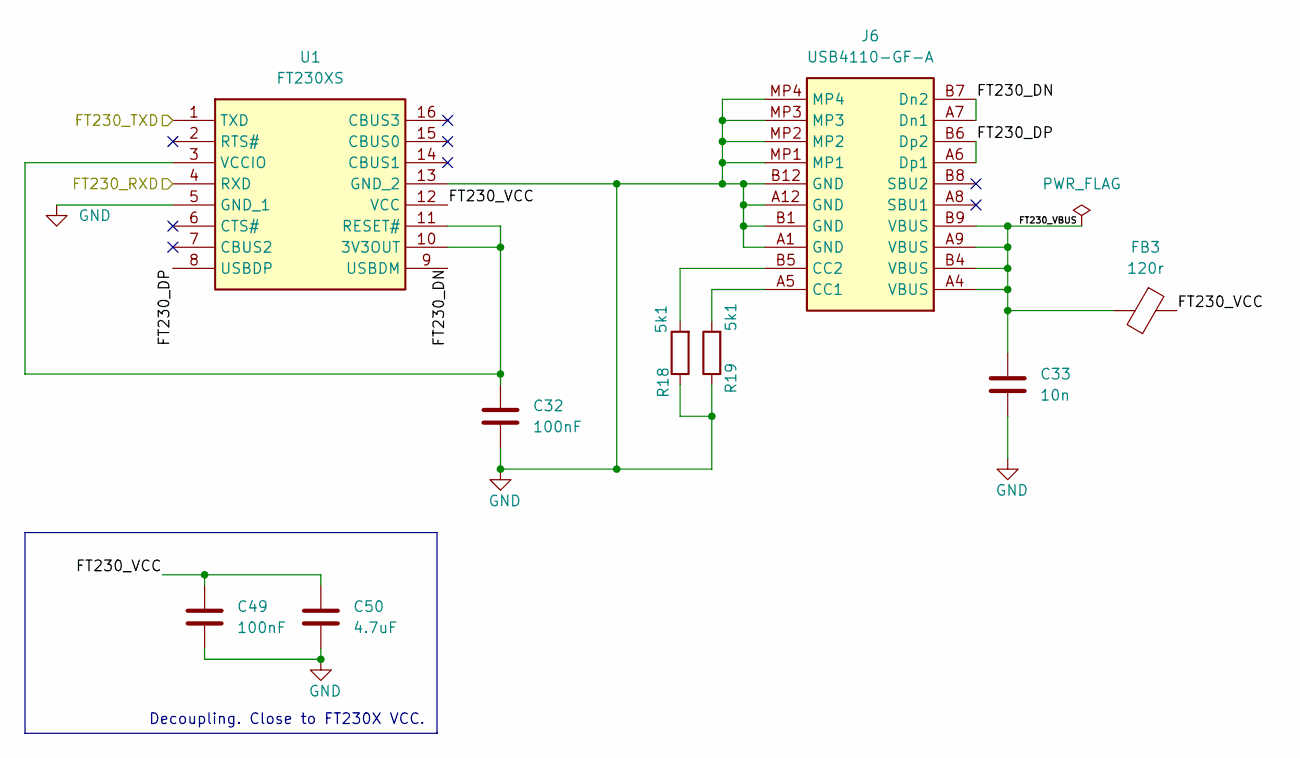
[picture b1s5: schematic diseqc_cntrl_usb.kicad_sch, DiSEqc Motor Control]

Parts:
C32, C49: 100nF; C_0603_1608Metric
C33: 10n; C_0603_1608Metric
C50: 4.7uF; C_0805_2012Metric
FB3: 120r; L_0603_1608Metric
J6: USB4110-GF-A; USB4110GFA; Mouser Part Number 640-USB4110-GF-A
R18, R19: 5k1; R_0603_1608Metric; Mouser Part Number 603-RC0603FR-075K1P
U1: FT230XS; SOP64P599X175-16N; Mouser Part Number 895-FT230XS-U

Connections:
/MCU/USART3_RX: U1.1 (TXD); also elsewhere on the board
/MCU/USART3_TX: U1.4 (RXD); also elsewhere on the board
/MCU/USB-UART/FT230_DN: J6.A7 (Dn1), J6.B7 (Dn2), U1.9 (USBDM)
/MCU/USB-UART/FT230_DP: J6.A6 (Dp1), J6.B6 (Dp2), U1.8 (USBDP)
/MCU/USB-UART/FT230_VBUS: C33.1, FB3.2, J6.A4 (VBUS), J6.A9 (VBUS), J6.B4 (VBUS), J6.B9 (VBUS)
/MCU/USB-UART/FT230_VCC: C49.1, C50.2, FB3.1, U1.12 (VCC)
GND: C32.2, C33.2, C49.2, C50.1, J6.A1 (GND), J6.A12 (GND), J6.B1 (GND), J6.B12 (GND), J6.MP1, J6.MP2, J6.MP3, J6.MP4, R18.1, R19.1, U1.5 (GND_1), U1.13 (GND_2); also elsewhere on the board
unnamed: J6.A5 (CC1), R19.2
unnamed: J6.B5 (CC2), R18.2
unnamed: C32.1, U1.3 (VCCIO), U1.10 (3V3OUT), U1.11 (RESET#)

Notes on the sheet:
Decoupling. Close to FT230X VCC.

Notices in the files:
firmware/targets-local/CUBLEY_F407_0_5/board.h:
Copyright (c) .NET Foundation and Contributors
See LICENSE.md file in the project root for full license information.
